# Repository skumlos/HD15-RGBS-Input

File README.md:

HD15/VGA Breakout for RGBS sources

This little PCB breaks out RGBS from a HD15/VGA plug, where sync is from the HSync/CSync pin 13.
It was originally designed to fit the Barco ADVM monitors if L77HDEH15SOL2RM8 or similar is used
as the HD15 port, and two 7mm M3 standoffs are used to fasten it to the monitor chassis.

The JP1 is for being able to send sync straight through, or sync can be dealt with just like the
other signals, with a voltage divider and a DC bias capacitor.

Blanking can be from 5V from the VGA port, but it is not normally available in VGA breakout cables.
Instead SW1 can be added, and the voltage it switches can be created with VCC and a voltage divider
consisting of R20 and R21, or VCC directly by closing JP2. All this is not tested as it doesn't fit
the ADVMs, instead auto blanking can be done by other measures.

(2023) Martin Hejnfelt (martin@hejnfelt.com)

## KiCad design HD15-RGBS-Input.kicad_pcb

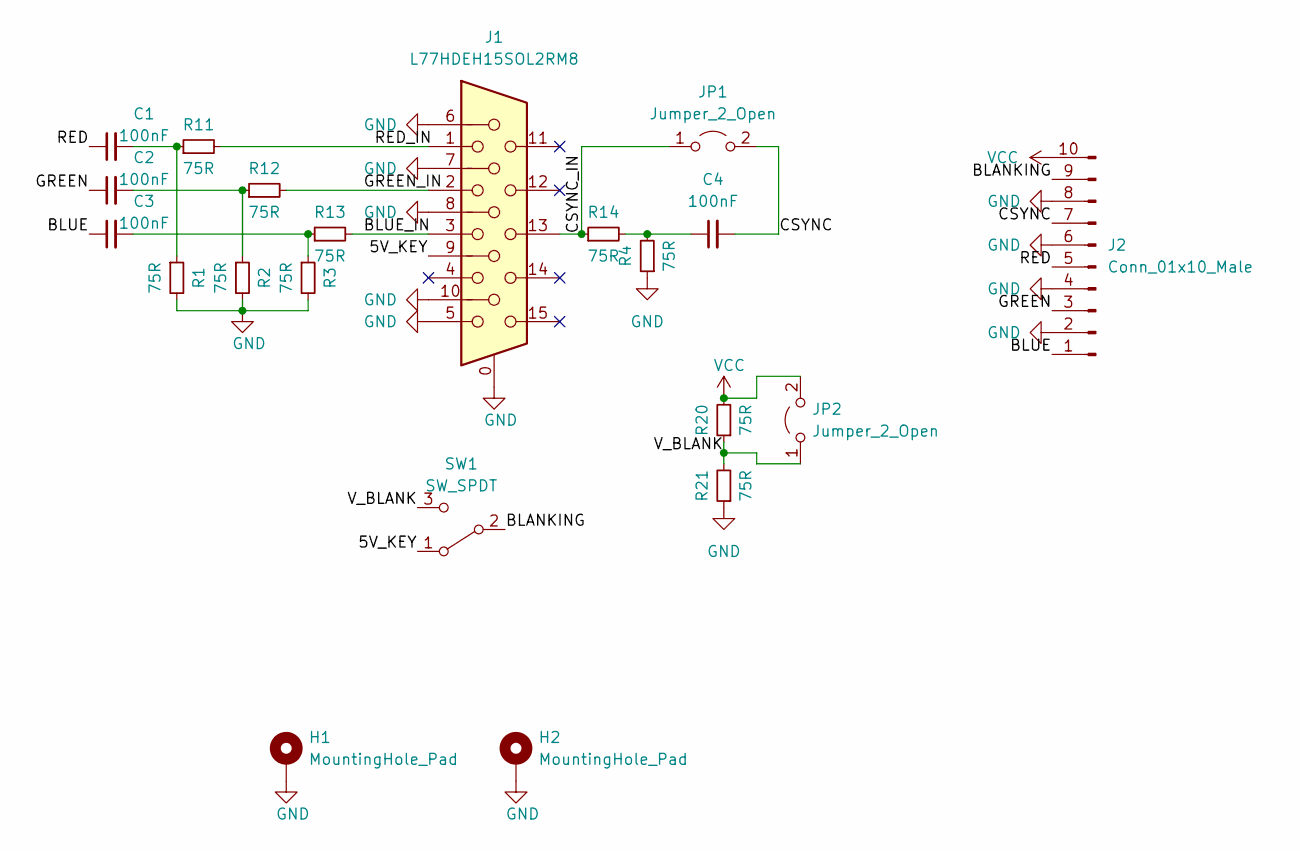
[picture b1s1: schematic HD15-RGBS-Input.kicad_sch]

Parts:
C1, C2, C3, C4: 100nF; C_0805_2012Metric_Pad1.18x1.45mm_HandSolder
H1, H2: MountingHole_Pad; MountingHole_3.2mm_M3_Pad
J1: L77HDEH15SOL2RM8; DSUB-15-HD_Female_Vertical_P2.29x1.98mm_MountingHoles
J2: Conn_01x10_Male; PinHeader_1x10_P2.54mm_Vertical
JP1, JP2: Jumper_2_Open; SolderJumper-2_P1.3mm_Open_TrianglePad1.0x1.5mm
R1, R2, R3, R4, R11, R12, R13, R14, R20, R21: 75R; R_0805_2012Metric_Pad1.20x1.40mm_HandSolder
SW1: SW_SPDT; SW_E-Switch_EG1271_SPDT

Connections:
/5V_KEY: J1.9, SW1.1 (A)
/BLANKING: J2.9, SW1.2 (B)
/BLUE: C3.1, J2.1
/BLUE_IN: J1.3, R13.2
/CSYNC: C4.2, J2.7, JP1.2 (B)
/CSYNC_IN: J1.13, JP1.1 (A), R14.1
/GREEN: C2.1, J2.3
/GREEN_IN: J1.2, R12.2
/RED: C1.1, J2.5
/RED_IN: J1.1, R11.2
/V_BLANK: JP2.1 (A), R20.1, R21.2, SW1.3 (C)
GND: H1.1, H2.1, J1.0, J1.5, J1.6, J1.7, J1.8, J1.10, J2.2, J2.4, J2.6, J2.8, R1.2, R2.2, R3.2, R4.1, R21.1
unnamed: C1.2, R1.1, R11.1
unnamed: C2.2, R2.1, R12.1
unnamed: C3.2, R3.1, R13.1
unnamed: C4.1, R4.2, R14.2
VCC: J2.10, JP2.2 (B), R20.2

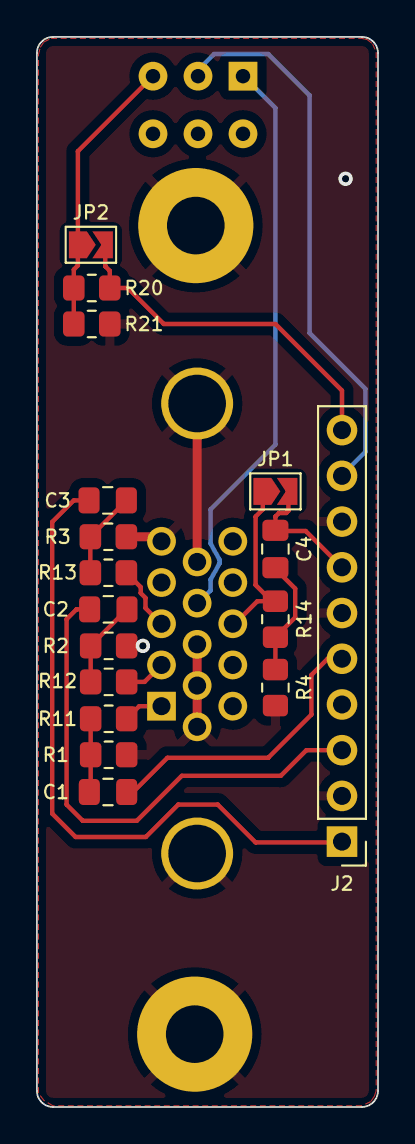
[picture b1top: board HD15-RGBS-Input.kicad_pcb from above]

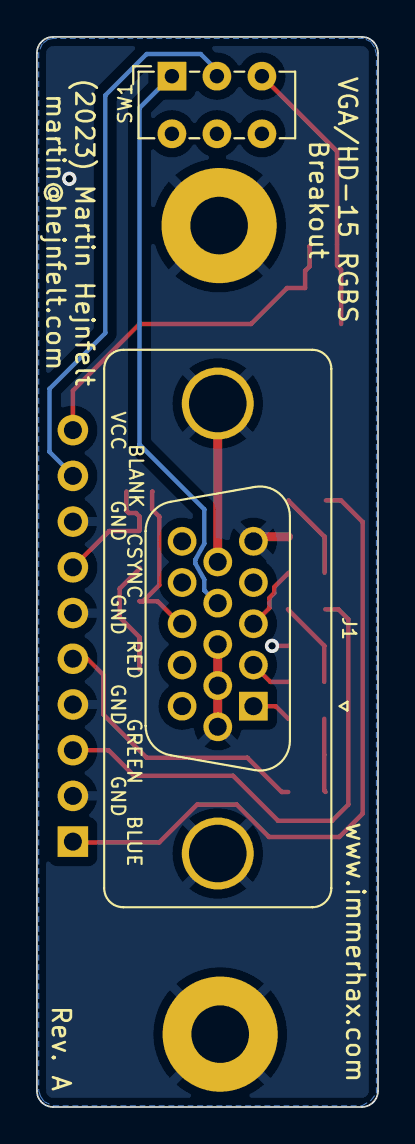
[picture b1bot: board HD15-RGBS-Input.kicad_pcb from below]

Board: 2 copper layers, 19.0 x 59.5 mm, 21 parts (4 on the bottom side), 17 nets.

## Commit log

2023-11-11 Add README
